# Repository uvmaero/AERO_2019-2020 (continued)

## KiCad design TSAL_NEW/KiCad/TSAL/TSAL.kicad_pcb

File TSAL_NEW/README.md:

# TSAL_NEW
TSAL Driver for FN and FH

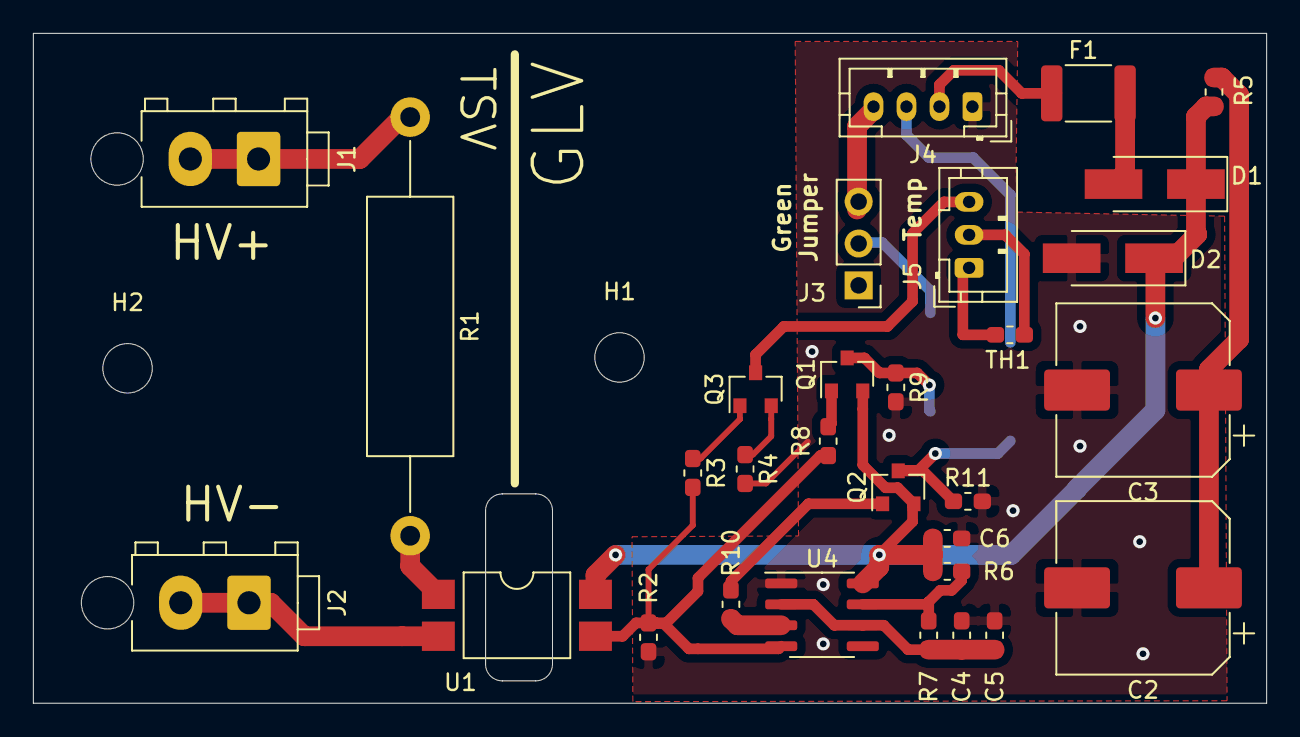
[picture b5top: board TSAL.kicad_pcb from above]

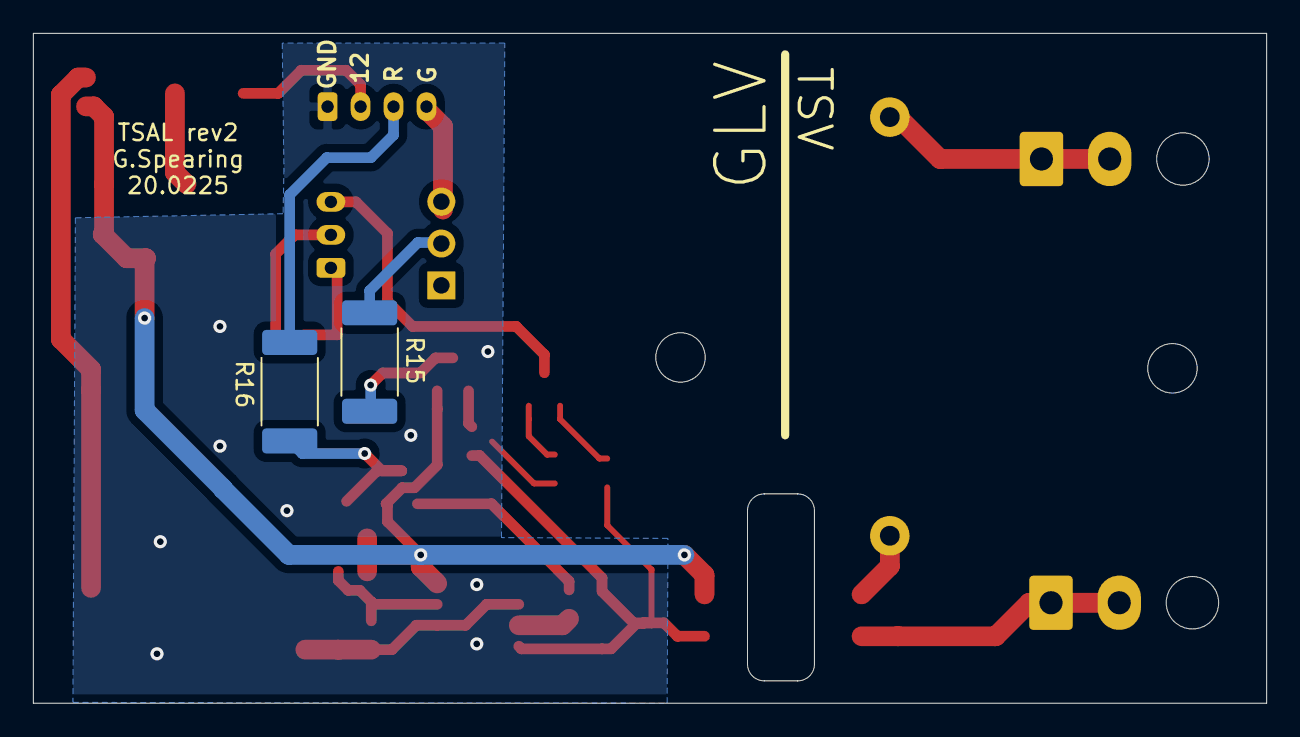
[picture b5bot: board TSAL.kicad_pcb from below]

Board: 2 copper layers, 74.8 x 40.6 mm, 34 parts (2 on the bottom side), 24 nets.

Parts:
C2, C3: 330uF; CP_Elec_10x10
C4, C5: 1u; C_0603_1608Metric_Pad1.05x0.95mm_HandSolder
C6: 0.1uF; C_0603_1608Metric_Pad1.05x0.95mm_HandSolder
D1: B340A-13-F1; D_SMA_Handsoldering
D2: ESD5Z12T1G; D_SMA_Handsoldering
F1: 1812L075/24; Fuse_1812_4532Metric_Pad1.30x3.40mm_HandSolder
H1, H2: MountingHole; MountingHole_3mm
J1: HV INPUT; TE_MATE-N-LOK_1-770866-x_1x02_P4.14mm_Vertical_ASM
J2: HV GND; TE_MATE-N-LOK_1-770866-x_1x02_P4.14mm_Vertical_ASM
J3: B3B-PH-K; PinHeader_1x03_P2.54mm_Vertical
J4: B4B-PH-K; JST_PH_B4B-PH-K_1x04_P2.00mm_Vertical
J5: Conn_01x02; JST_PH_B3B-PH-K_1x03_P2.00mm_Vertical
Q1, Q2: BSS84; SOT-23
Q3: 2N7002; SOT-23
R1: ROX3SJ39K; R_Axial_DIN0516_L15.5mm_D5.0mm_P25.40mm_Horizontal
R2, R9, R11: 10k; R_0603_1608Metric_Pad1.05x0.95mm_HandSolder
R3, R4, R8, R10: 100; R_0603_1608Metric_Pad1.05x0.95mm_HandSolder
R5: 2; R_0603_1608Metric_Pad1.05x0.95mm_HandSolder
R6: 100k; R_0603_1608Metric_Pad1.05x0.95mm_HandSolder
R7: 235k; R_0603_1608Metric_Pad1.05x0.95mm_HandSolder
R15, R16: 100; R_2512_6332Metric_Pad1.52x3.35mm_HandSolder
TH1: NCU18XH103F60RB; R_0603_1608Metric_Pad1.05x0.95mm_HandSolder
U1: LTV-817S; SMDIP-4_W9.53mm
U4: LM555; SOIC-8_3.9x4.9mm_P1.27mm

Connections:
+12V: C6.1, D1.1, D2.1, Q1.2, Q2.2, R5.2, R6.1, U1.4, U4.8
/12V_CAP: C2.1, C3.1, R5.1
/555_OUTPUT: R10.2, U4.3
/DIS: R6.2, R7.1, U4.7
/GLV+: F1.2, J4.2
/HV+: J1.1, J1.2, R1.1
/HV_PRES: R2.1, R3.2, R8.2, U1.3, U4.4
/HV_PRES_TRUE: J5.3, Q3.3
/LED_GREEN+: J3.3, J4.4
/LED_GREEN_OUT: J3.2, R15.1
/LED_RED+: J4.3, R16.1
/RED_FET: Q2.1, R10.1
/THM: J5.1, TH1.1
/THR: C4.1, C5.1, R7.2, U4.2, U4.6
GND: C2.2, C3.2, C4.2, C5.2, C6.2, D2.2, J4.1, R2.2, R4.2, R9.2, R11.2, U4.1
GNDA: J2.1, J2.2, U1.2
unnamed: D1.2, F1.1
unnamed: J5.2, TH1.2
unnamed: Q1.1, R8.1
unnamed: Q1.3, R9.1, R15.2
unnamed: Q2.3, R11.1, R16.2
unnamed: Q3.1, R3.1
unnamed: Q3.2, R4.1
unnamed: R1.2, U1.1

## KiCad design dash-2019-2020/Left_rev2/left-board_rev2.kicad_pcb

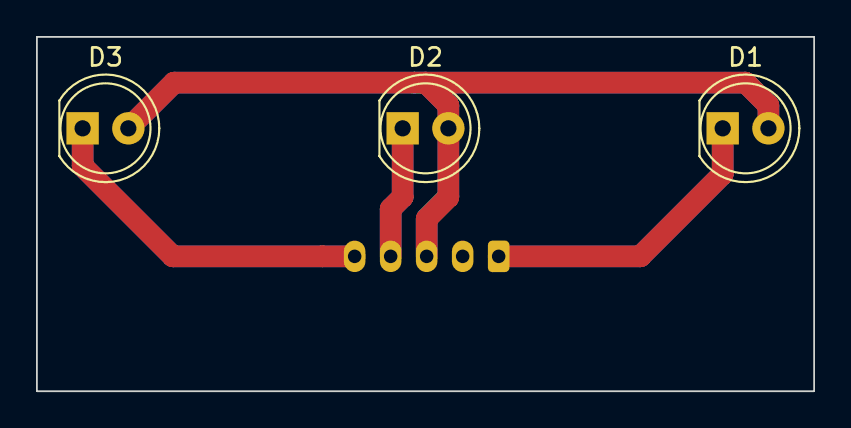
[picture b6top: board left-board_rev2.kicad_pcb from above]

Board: 2 copper layers, 43.2 x 19.7 mm, 4 parts (1 on the bottom side), 4 nets.

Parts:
D1: FAULT_IND_1; LED_D5.0mm
D2: FAULT_IND_2; LED_D5.0mm
D3: FAULT_IND_3; LED_D5.0mm
J1: B5B-PH-SM4-TB(LF)(SN); JST_PH_S5B-PH-K_1x05_P2.00mm_Horizontal

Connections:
+5V: D1.2, D2.2, D3.2, J1.3
/~FAULT_IND_1: D3.1, J1.5
/~FAULT_IND_2: D2.1, J1.4
/~FAULT_IND_3: D1.1, J1.1

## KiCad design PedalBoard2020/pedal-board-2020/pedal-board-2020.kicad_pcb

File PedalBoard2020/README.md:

Pedal Board for CS4.5

This board will have CAN interface, both in and out.

Will take Pedal Acceleration values.

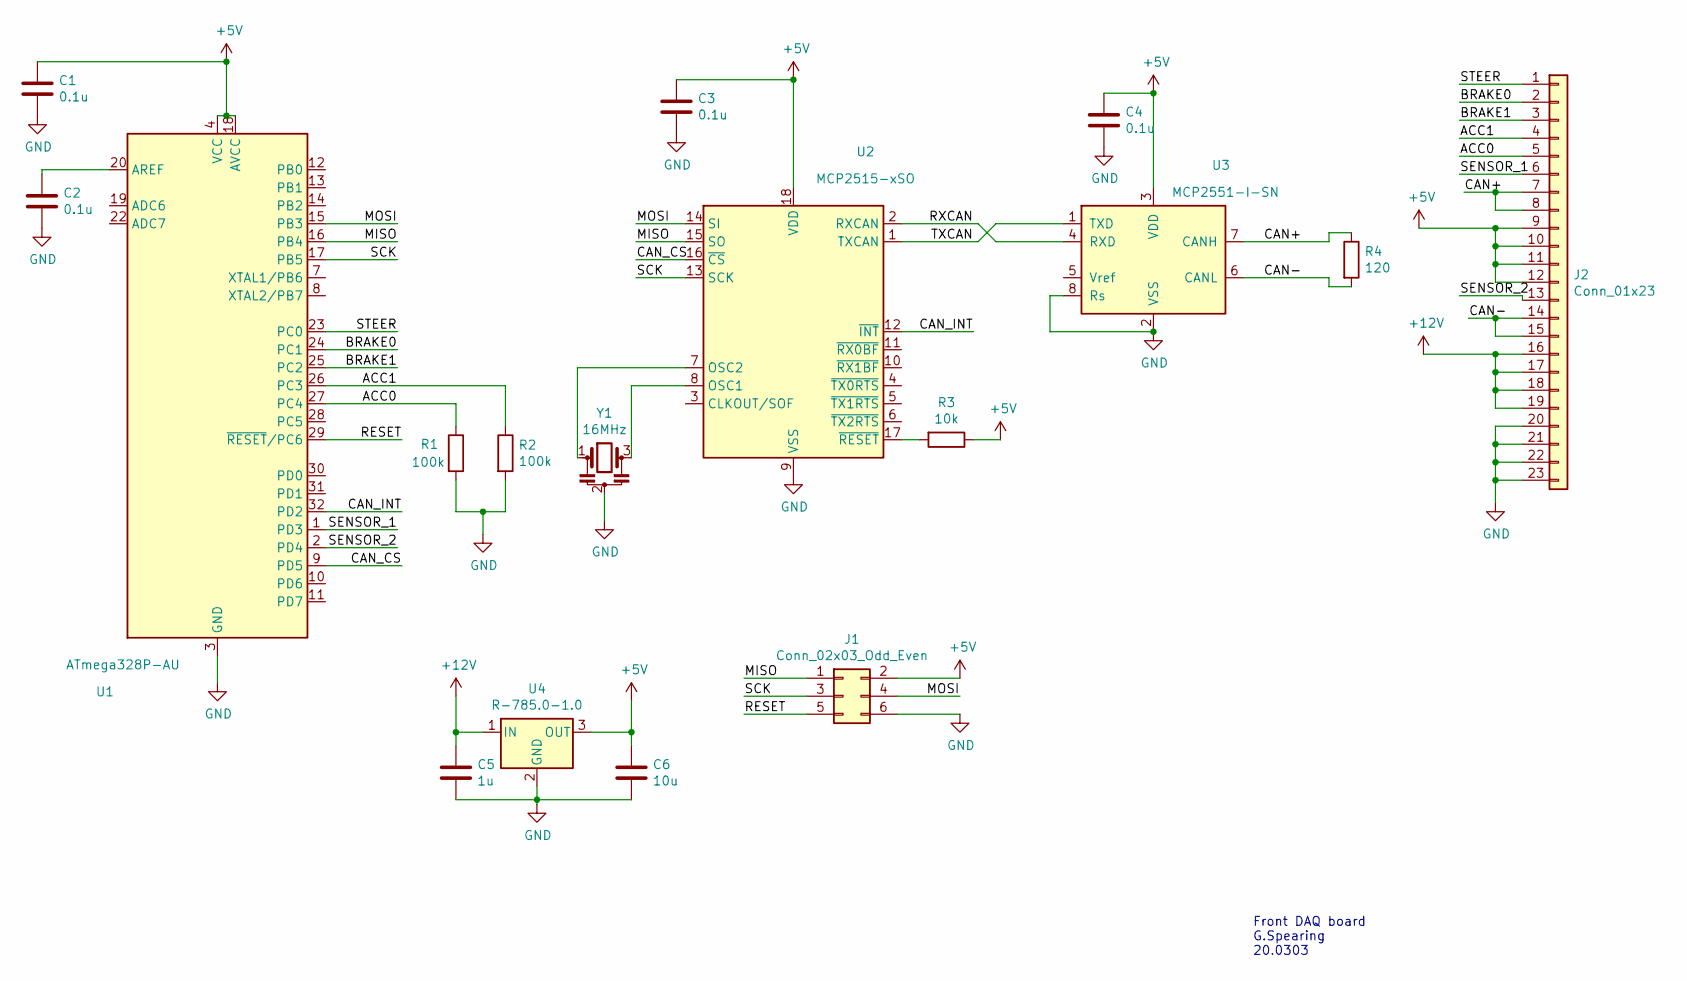
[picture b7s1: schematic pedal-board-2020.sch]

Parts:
C1, C2, C3, C4: 0.1u; C_0603_1608Metric_Pad1.05x0.95mm_HandSolder
C5: 1u; C_0603_1608Metric_Pad1.05x0.95mm_HandSolder
C6: 10u; C_0603_1608Metric_Pad1.05x0.95mm_HandSolder
J1: Conn_02x03_Odd_Even; PinHeader_2x03_P2.54mm_Vertical
J2: Conn_01x23; TE_AMPSEAL_1-776087-x_3Rows_23_P0.4mm_Horizontal
R1, R2: 100k; R_0603_1608Metric_Pad1.05x0.95mm_HandSolder
R3: 10k; R_0603_1608Metric_Pad1.05x0.95mm_HandSolder
R4: 120; R_0603_1608Metric_Pad1.05x0.95mm_HandSolder
U1: ATmega328P-AU; TQFP-32_7x7mm_P0.8mm
U2: MCP2515-xSO; SOIC-18W_7.5x11.6mm_P1.27mm
U3: MCP2551-I-SN; SOIC-8_3.9x4.9mm_P1.27mm
U4: R-785.0-1.0; Converter_DCDC_RECOM_R-78E-0.5_THT
Y1: 16MHz; Resonator_SMD_muRata_CSTxExxV-3Pin_3.0x1.1mm_HandSoldering

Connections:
+5V: C1.1, C3.1, C4.1, C6.1, J1.2, J2.9, J2.10, J2.11, J2.12, R3.1, U1.4 (VCC), U1.6 (VCC), U1.18 (AVCC), U2.18 (VDD), U3.3 (VDD), U4.3 (OUT)
+12V: C5.2, J2.16, J2.17, J2.18, J2.19, U4.1 (IN)
/ACC0: J2.5, R1.1, U1.27 (PC4)
/ACC1: J2.4, R2.1, U1.26 (PC3)
/BRAKE0: J2.2, U1.24 (PC1)
/BRAKE1: J2.3, U1.25 (PC2)
/CAN+: J2.7, J2.8, R4.1, U3.7 (CANH)
/CAN-: J2.14, J2.15, R4.2, U3.6 (CANL)
/CAN_CS: U1.9 (PD5), U2.16 (~CS)
/CAN_INT: U1.32 (PD2), U2.12 (~INT)
/MISO: J1.1, U1.16 (PB4), U2.15 (SO)
/MOSI: J1.4, U1.15 (PB3), U2.14 (SI)
/RESET: J1.5, U1.29 (~RESET~/PC6)
/RXCAN: U2.2 (RXCAN), U3.4 (RXD)
/SCK: J1.3, U1.17 (PB5), U2.13 (SCK)
/SENSOR_1: J2.6, U1.1 (PD3)
/SENSOR_2: J2.13, U1.2 (PD4)
/STEER: J2.1, U1.23 (PC0)
/TXCAN: U2.1 (TXCAN), U3.1 (TXD)
GND: C1.2, C2.2, C3.2, C4.2, C5.1, C6.2, J1.6, J2.20, J2.21, J2.22, J2.23, R1.2, R2.2, U1.3 (GND), U1.5 (GND), U1.21 (GND), U2.9 (VSS), U3.2 (VSS), U3.8 (Rs), U4.2 (GND), Y1.2
unnamed: C2.1, U1.20 (AREF)
unnamed: R3.2, U2.17 (~RESET)
unnamed: U2.7 (OSC2), Y1.1
unnamed: U2.8 (OSC1), Y1.3

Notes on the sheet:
Front DAQ board G.Spearing 20.0303

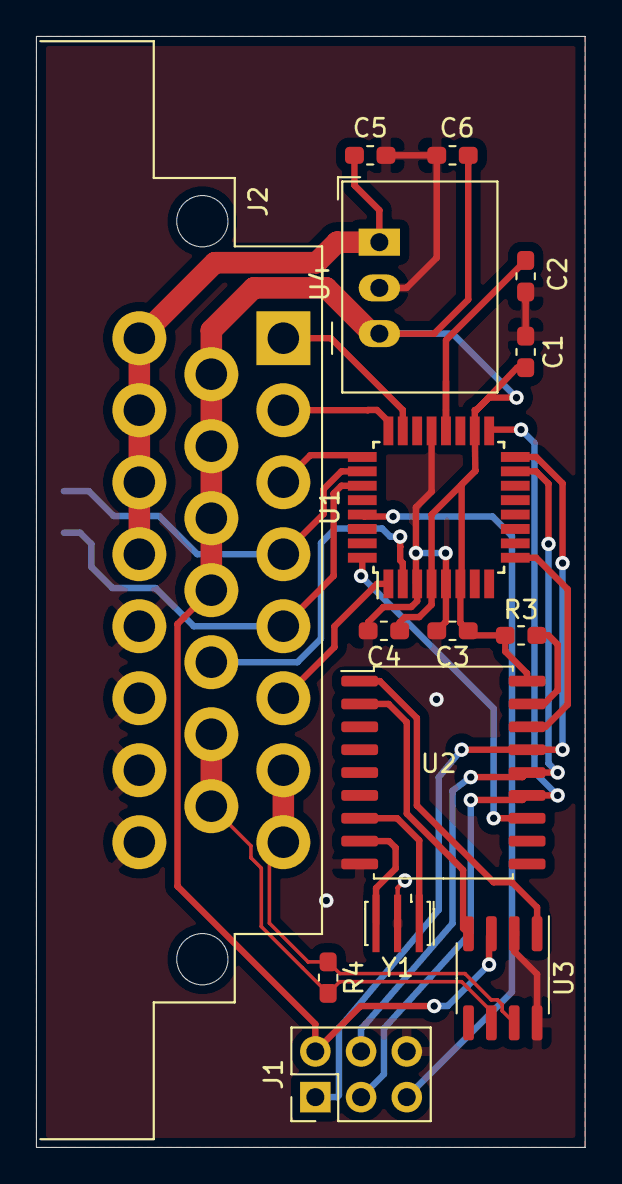
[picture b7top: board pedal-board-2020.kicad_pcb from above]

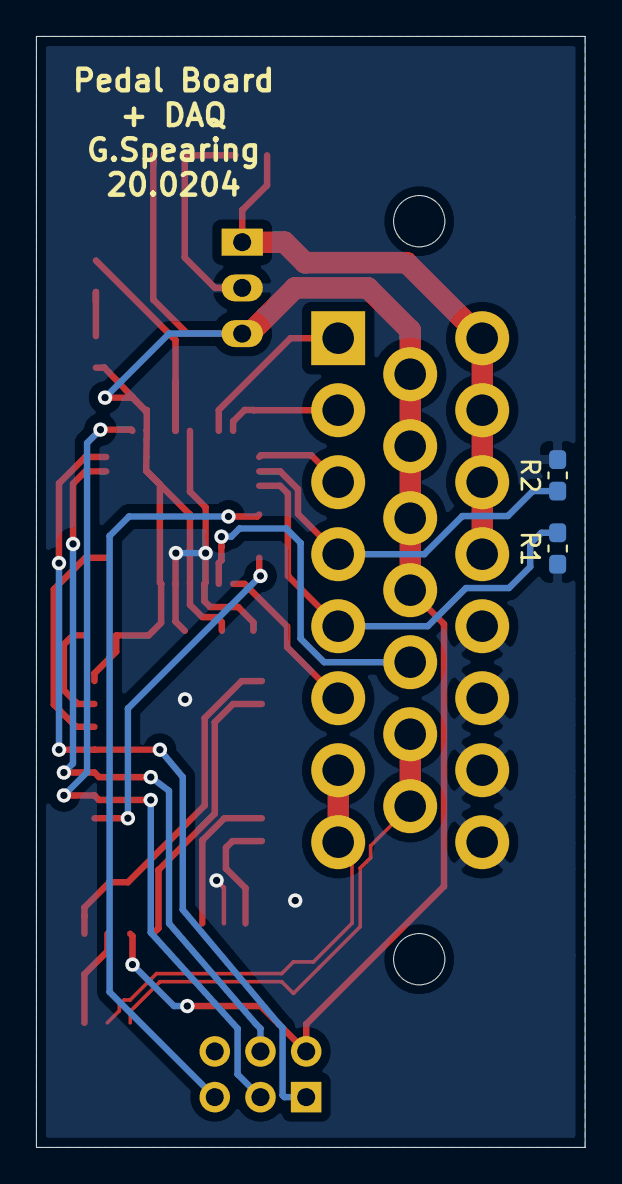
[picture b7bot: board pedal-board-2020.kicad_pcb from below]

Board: 2 copper layers, 30.5 x 61.7 mm, 17 parts (2 on the bottom side), 24 nets.

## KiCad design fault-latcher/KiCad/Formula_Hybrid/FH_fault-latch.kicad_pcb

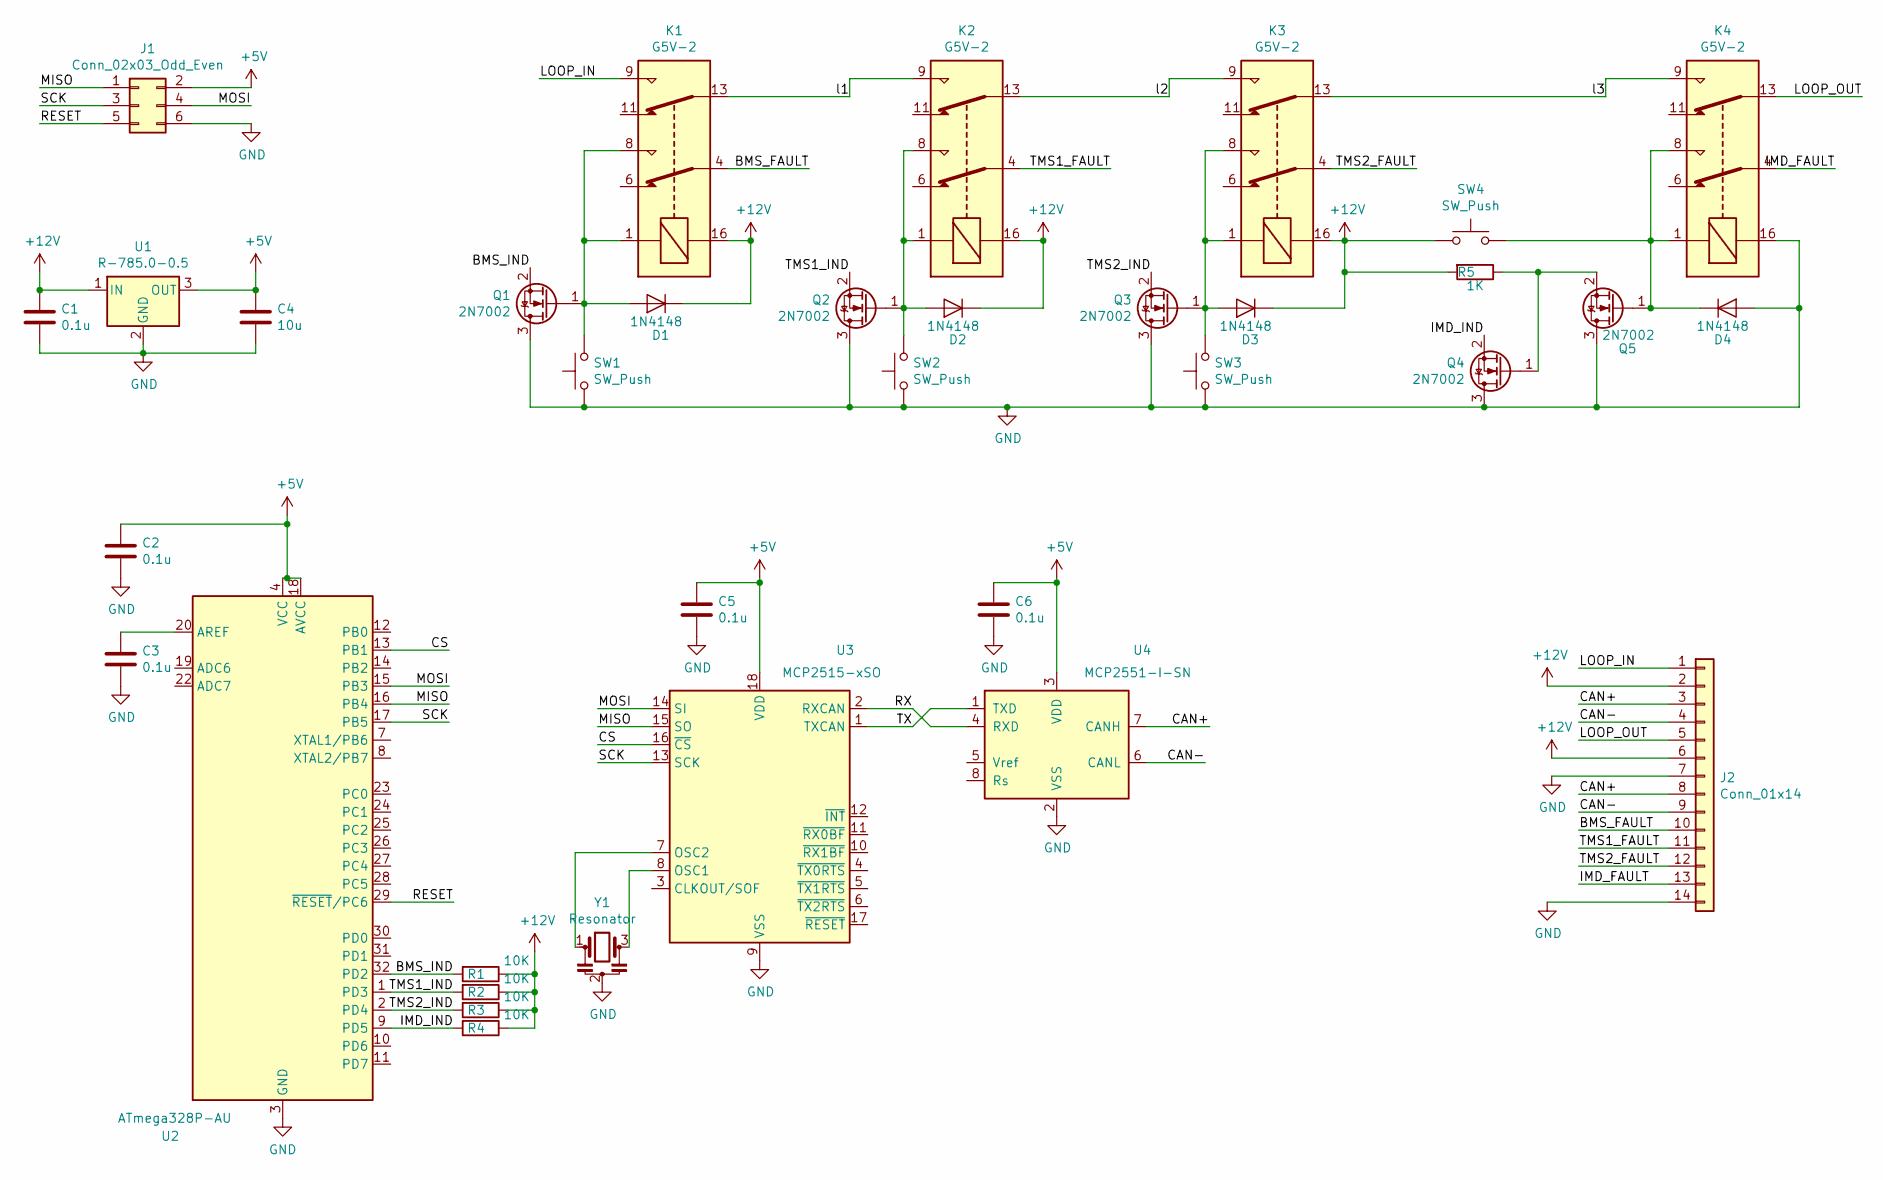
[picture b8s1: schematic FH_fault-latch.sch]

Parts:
C1, C2, C3, C5, C6: 0.1u; C_0603_1608Metric_Pad1.05x0.95mm_HandSolder
C4: 10u; C_0603_1608Metric_Pad1.05x0.95mm_HandSolder
D1, D2, D3, D4: 1N4148; D_SOD-123
J1: Conn_02x03_Odd_Even; PinSocket_2x03_P2.54mm_Vertical
J2: Conn_01x14; TE_1-776266-1_14pin_Horizontal
K1, K2, K3, K4: G5V-2; Relay_DPDT_Omron_G5V-2
Q1, Q2, Q3, Q4, Q5: 2N7002; SOT-23
R1, R2, R3, R4: 10K; R_0603_1608Metric_Pad1.05x0.95mm_HandSolder
R5: 1K; R_0603_1608Metric_Pad1.05x0.95mm_HandSolder
SW1, SW2, SW3, SW4: SW_Push; JST_PH_B2B-PH-K_1x02_P2.00mm_Vertical
U1: R-785.0-0.5; Converter_DCDC_RECOM_R-78E-0.5_THT
U2: ATmega328P-AU; TQFP-32_7x7mm_P0.8mm
U3: MCP2515-xSO; SOIC-18W_7.5x11.6mm_P1.27mm
U4: MCP2551-I-SN; SOIC-8_3.9x4.9mm_P1.27mm
Y1: Resonator; Resonator_SMD_muRata_CSTxExxV-3Pin_3.0x1.1mm_HandSoldering

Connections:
+5V: C2.1, C4.1, C5.1, C6.1, J1.2, U1.3 (OUT), U2.4 (VCC), U2.6 (VCC), U2.18 (AVCC), U3.18 (VDD), U4.3 (VDD)
+12V: C1.1, D1.1 (K), D2.1 (K), D3.1 (K), J2.2, J2.6, K1.16, K2.16, K3.16, R1.1, R2.1, R3.1, R4.1, R5.2, SW4.1, U1.1 (IN)
/BMS_FAULT: J2.10, K1.4
/BMS_IND: Q1.2 (S), R1.2, U2.32 (PD2)
/CAN+: J2.3, J2.8, U4.7 (CANH)
/CAN-: J2.4, J2.9, U4.6 (CANL)
/CS: U2.13 (PB1), U3.16 (~CS)
/IMD_FAULT: J2.13, K4.4
/IMD_IND: Q4.2 (S), R4.2, U2.9 (PD5)
/LOOP_IN: J2.1, K1.9
/LOOP_OUT: J2.5, K4.13
/MISO: J1.1, U2.16 (PB4), U3.15 (SO)
/MOSI: J1.4, U2.15 (PB3), U3.14 (SI)
/RESET: J1.5, U2.29 (~RESET~/PC6)
/RX: U3.2 (RXCAN), U4.4 (RXD)
/SCK: J1.3, U2.17 (PB5), U3.13 (SCK)
/TMS1_FAULT: J2.11, K2.4
/TMS1_IND: Q2.2 (S), R2.2, U2.1 (PD3)
/TMS2_FAULT: J2.12, K3.4
/TMS2_IND: Q3.2 (S), R3.2, U2.2 (PD4)
/TX: U3.1 (TXCAN), U4.1 (TXD)
/l1: K1.13, K2.9
/l2: K2.13, K3.9
/l3: K3.13, K4.9
GND: C1.2, C2.2, C3.2, C4.2, C5.2, C6.2, D4.2 (A), J1.6, J2.7, J2.14, K4.16, Q1.3 (D), Q2.3 (D), Q3.3 (D), Q4.3 (D), Q5.3 (D), SW1.1, SW2.1, SW3.1, U1.2 (GND), U2.3 (GND), U2.5 (GND), U2.21 (GND), U3.9 (VSS), U4.2 (VSS), Y1.2
unnamed: C3.1, U2.20 (AREF)
unnamed: D1.2 (A), K1.1, K1.8, Q1.1 (G), SW1.2
unnamed: D2.2 (A), K2.1, K2.8, Q2.1 (G), SW2.2
unnamed: D3.2 (A), K3.1, K3.8, Q3.1 (G), SW3.2
unnamed: D4.1 (K), K4.1, K4.8, Q5.1 (G), SW4.2
unnamed: Q4.1 (G), Q5.2 (S), R5.1
unnamed: U3.7 (OSC2), Y1.1
unnamed: U3.8 (OSC1), Y1.3

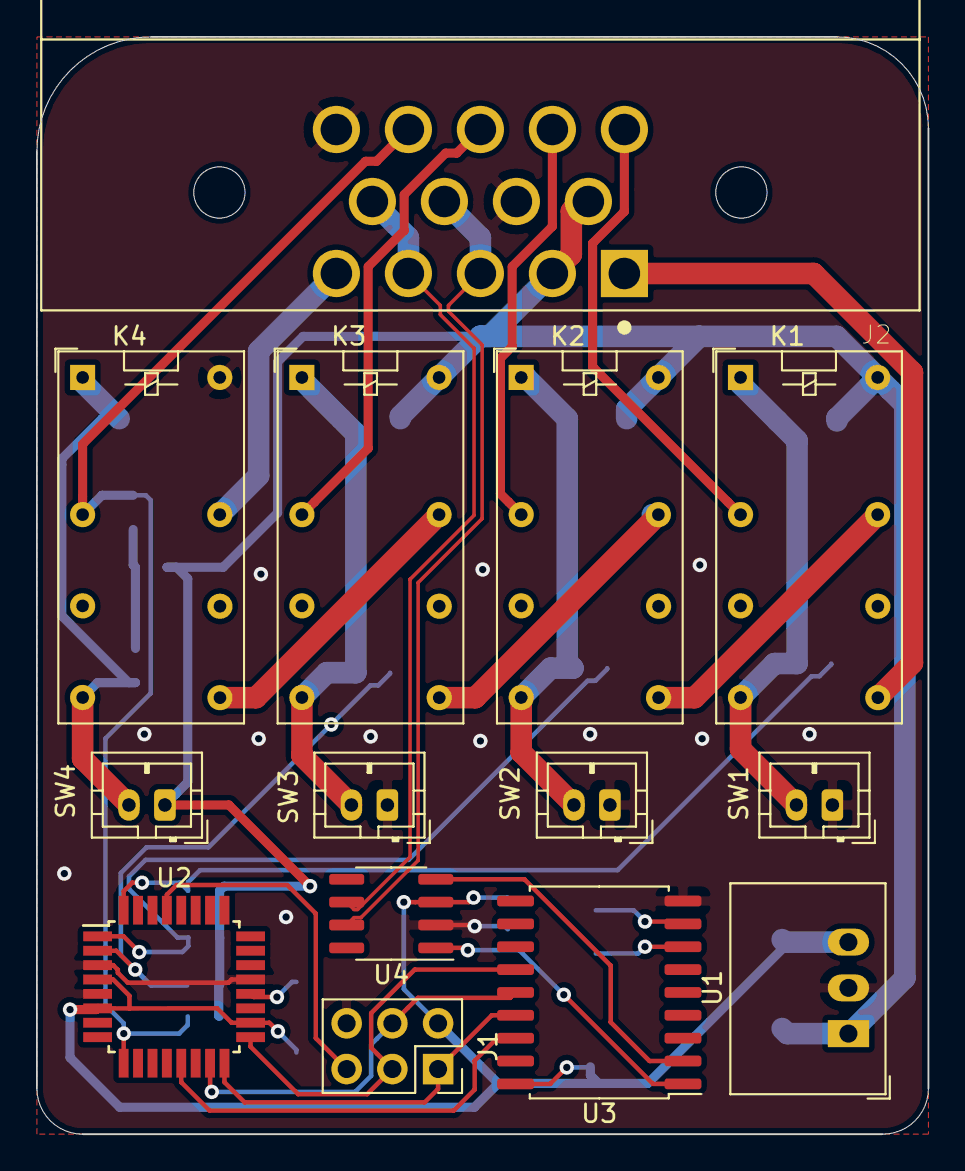
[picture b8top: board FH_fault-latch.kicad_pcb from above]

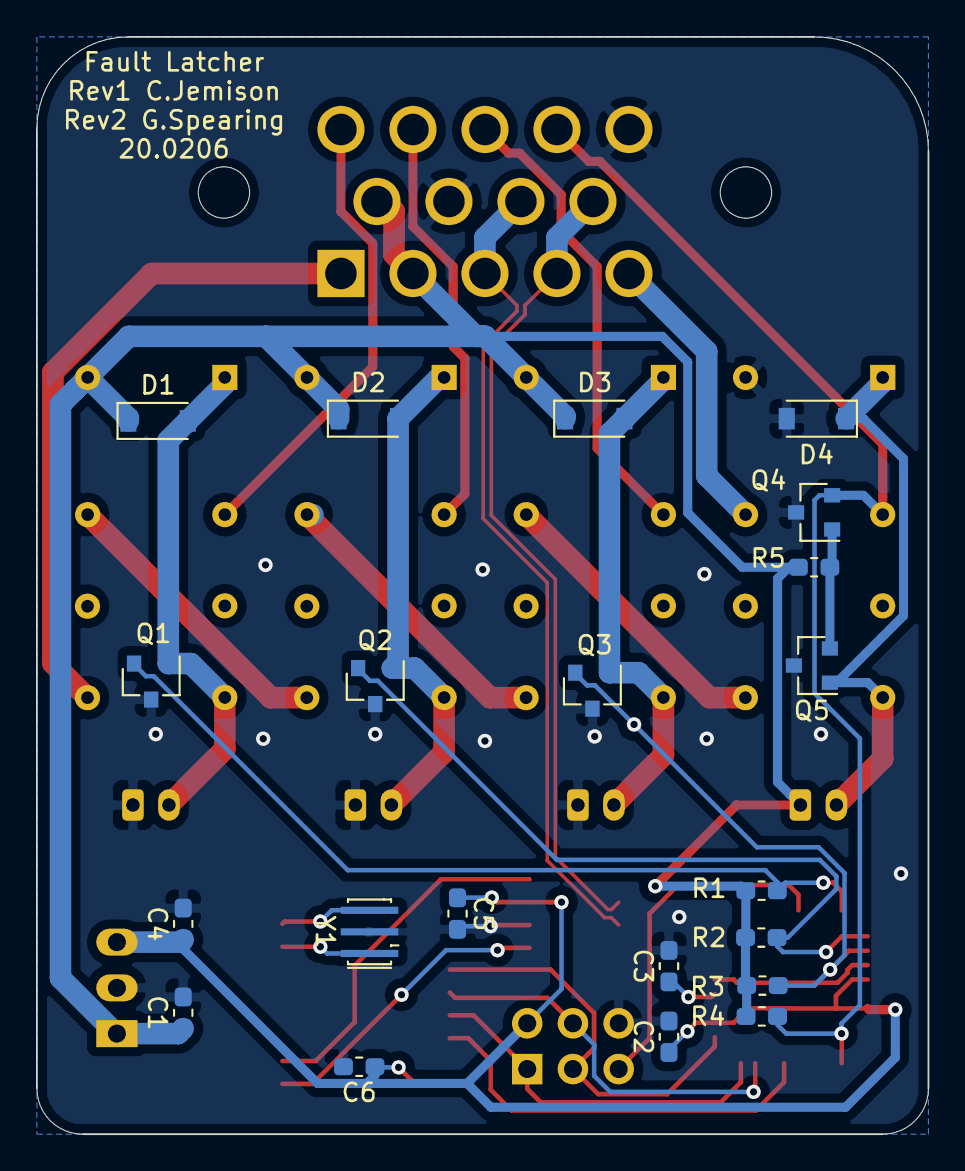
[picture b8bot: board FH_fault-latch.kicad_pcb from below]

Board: 2 copper layers, 49.5 x 61.0 mm, 35 parts (21 on the bottom side), 33 nets.

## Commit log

2020-01-28 Moved files to 2019-2020 repo
2020-01-28 Moved to 2019-2020 repo
2020-01-28 add Fault-latcher folder
2020-01-28 init BSPD folder
2020-01-28 formula north
2020-01-28 Add HV LED board
2020-01-28 start kicad
2020-01-29 Hybrid Red Blink Blink
2020-01-29 Fix HV Ind BOM, prep for gerbers
2020-01-29 Add BSPD
2020-01-29 Outputs for HV Indicator
2020-01-29 Renders
2020-01-29 More TSAL work
    More TSAL work
2020-01-29 Reorganize 60V_IND
2020-01-29 add Green LED driver
2020-01-30 Major SCH fix on BSPD
2020-01-30 Remove ground isolation, fix buffer for HV Interface board from current monitor
2020-01-30 TSAL Comments
2020-01-30 fix the fixes
2020-01-30 60V_IND and BSPD RTM
2020-01-30 schem ready for review
2020-01-31 Ready for Review
2020-01-31 Ready for Reivew
2020-01-31 Fix PDF Documents of BSPD
2020-01-31 Suggested revisions of TSAL from review
2020-02-01 Final Schem - No Boost
2020-02-01 current HV interface board
2020-02-01 Final PCB
2020-02-02 Soft Shutdown Circuit
2020-02-02 Added logos
2020-02-03 TSAL Review complete
2020-02-03 Fix altium boards, prep for output
2020-02-03 other edits (fix tracks that ran into pads at angles)
2020-02-04 First Rev Pedal Board + Front DAQ
2020-02-04 init firmware for front pedal board
2020-02-05 2-5-20 wip
2020-02-05 add rth
2020-02-05 init LED board
2020-02-05 I think its done, will do final review and reorg repo
2020-02-05 updated PCB and SCH
2020-02-05 Create PCB
2020-02-06 PCB ready
2020-02-07 PCB Design ready to ship
2020-02-07 add extra sensor
2020-02-07 Final Layout
2020-02-07 Layout Rev2
2020-02-07 THEORETICALLY DONE
2020-02-07 added LED resistors on output
2020-02-07 Gerber Zip Files ready to ship
2020-02-07 altium gerbers ready, merging into master
2020-02-07 Update BSPD and HV Ind
    add rth
    I think its done, will do final review and reorg repo
    THEORETICALLY DONE
    altium gerbers ready, merging into master
2020-02-07 Gerber fixes, outputs
2020-02-10 small updates
2020-02-10 Initial work on HV PDU
2020-02-10 Dash 3D
2020-02-10 3d updates
2020-02-14 Altium work on HV stuff
2020-02-16 BMS init
2020-02-17 BMS schem
2020-02-18 final schem
2020-02-19 HV Altium work continues
2020-02-20 more work
2020-02-21 LV breakout board
2020-02-21 minor FH Chnage look at FN
2020-02-21 start modifications
2020-02-21 minor changes for next rev
2020-02-21 minor changes
2020-02-21 finish sch and ready for review
2020-02-21 Footprint updates of GLV board, pull the libraries repo please!
2020-02-22 Final fixes to GLV board so it works with HV board
2020-02-23 LVPDU schem and pcb
2020-02-24 HV Int board work
2020-02-24 file reorg
2020-02-25 More HV box work
2020-02-25 second revision
2020-02-25 Changed HVInput to Optoisolator and added HV sense pin
2020-02-25 change resistor
2020-02-25 change port panel
2020-02-29 Updated PCB Layout
2020-02-29 change pcb trace
2020-03-02 Minor Layout Changes
2020-03-02 Change trace and create Gerber
2020-03-04 remove external ports and simplify left dash
2020-03-04 Minor changes / updates
2020-03-09 layout changes
2020-03-09 init review
2020-03-10 Review dash
2020-03-10 PCB layoutchanges
2020-03-10 create gerbers
2020-03-10 add notes for future
2020-03-16 Create port panel model with connectors
2020-03-16 update gitignore
2020-03-16 all HV work in altium
2020-03-16 Update 3d of lv breakout
2020-03-18 start documentation
2020-03-18 remove old interface board, docs for Vicor socket
2020-03-18 Add sim to DCDC, note down minor HV Interface issue
    repour all polys on HV INT before mfg!!
2020-03-18 update port panel 3d
2020-10-30 "update old library"
2020-11-06 change board function
2020-11-06 update design
2020-11-11 update code functionality per board
2020-11-18 minor updates
2020-11-19 change data timing
2020-11-19 update CAN libaray
2020-11-19 remove duplicate libaray
2020-11-19 add temperature
2020-11-20 add Rinehart Messages
